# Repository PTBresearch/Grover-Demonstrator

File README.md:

# Grover-Demonstrator
A simple hardware demonstrator to let the user experience classical search in unstructured data, vs the Grover quantum computer algorithm.

## What can it be used for?

- [Showing how (computationally) hard it is to find something in unstructured data](#showing-how-computationally-hard-it-is-to-find-something-in-unstructured-data)
- [Showing the "quantum advantage" that the Grover algorithm can provide](#showing-the-quantum-advantage-that-the-grover-algorithm-can-provide)
- [Showing the relationship between shots and the probability distribution](#showing-the-relationship-between-shots-and-the-probability-distribution)
- [Showing the impact of noise on the results of quantum computers / the Grover algorithm](#showing-the-impact-of-noise-on-the-results-of-quantum-computers--the-grover-algorithm)
- [Attracting people to a booth by having it blink](#attracting-people-to-a-booth-by-having-it-blink)

## Device overview

| Control | Description |
|---|---|
| On/off switch (top) | Turns the demonstrator on/off. |
| Charging port (top) | Use a USB-A to USB-C cable. When fully charged, the device can run for ~15 h. |
| Model slider (top) | Selects one of the 3 models for "Quantum Computer" mode. |
| Round button (top right) | Switches between "Probability View" and "Shot View". Only in "Quantum Computer" mode. |
| "Classical Computer" button | Starts in "Classical Computer" mode. |
| "Quantum Computer" button | Starts in "Quantum Computer" mode. |
| Left display | Number of button presses needed the last time "Classical Computer" mode was used. |
| Right display | Number of button presses needed the last time "Quantum Computer" mode was used. |
| Blue button | Runs 1 iteration of the Grover algorithm. |
| 8 × 8 button grid | 64 buttons, one of which is searched. Non-pressed buttons light up based on the current view. |

## Showing how (computationally) hard it is to find something in unstructured data

1. Start the demonstrator in "Classical Computer" mode and give it to a user.
2. Their task is to find the one button (of the 64 square ones) that blinks green when pushed.
3. This is an example of search in unstructured data: the user has no idea which button will light green.
4. You can discuss with them that with 64 buttons, they will need 32 tries on average.

A good example of search in unstructured data is guessing a password or decrypting data with no information about the key. You can verify that a solution is correct (you can try to decrypt the data), but there are no strategies to speed up the search. This is different from search problems with structured data, where you can, for example, sort the data to make it easier to search through.

Buttons that have not been pressed glow in a blue hue. The brighter they are, the more likely they are the correct button. As the data are unstructured, all buttons glow equally bright, but they become brighter as fewer buttons are left to be pressed.

> [!TIP]
> If the user found the green button in just a few steps, you can ask them or someone else to try again.

## Showing the "quantum advantage" that the Grover algorithm can provide

1. The user should have used/seen the "Classical Computer" mode already.
2. Make sure the demonstrator uses the **"Ideal"** model.
3. Start "Quantum Computer" mode. The user must again find the green button, ideally with fewer button presses. You can either let them search or do it yourself.

Again, buttons that have not been pressed glow in a blue hue. The brighter they are, the more likely they are the correct button. Initially, all buttons are equally bright, as there is no information about the correct result.

The user can "spend" a button press by pressing the blue button, which causes the Grover search algorithm to improve the prediction of the button that is searched.

When the blue button has been pressed 6 times, the prediction will be best. You can "undo" blue button presses by pressing the "Classical Computer" button. This is sometimes helpful when explaining the algorithm.

Thus, the optimal strategy seems to be to press the blue button once, then the brightest button. This strategy is less ideal with noise and high shot costs.

## Showing the relationship between shots and the probability distribution

1. The user should have used/seen the "Classical Computer" mode already.
2. Start "Quantum Computer" mode. The user must again find the green button, ideally with fewer button presses. You can either let them search or do it yourself.
3. Press the round button at the top of the device to switch to "Shot" mode.

In Shot mode, the buttons do not glow based on their likelihood. Instead, individual shots of the quantum computer are simulated. After the Grover algorithm is computed, the quantum state is read out, resulting in one random result based on the probabilities given by the quantum state of the qubits.

This mode makes it much more difficult to find the correct result without the ideal number of Grover algorithm iterations (blue button presses), especially when the "Real" model is used.

## Showing the impact of noise on the results of quantum computers / the Grover algorithm

1. The user should have used/seen the "Classical Computer" mode already.
2. Start "Quantum Computer" mode. The user must again find the green button, ideally with fewer button presses. You can either let them search or do it yourself.
3. When the blue Grover button has been pressed a few times, use the slider at the top to change between models:
   - **Ideal**: Simulation of a quantum computer without any noise/errors.
   - **Model**: Simple error model that introduces some gate errors.
   - **Real**: Results from a real IBM quantum computer.

The difference between the models is most easily visible when the buttons show probabilities, but Shot mode can also be used.

## Attracting people to a booth by having it blink

1. Start the device in "Quantum Computer" mode and press the round button on the top to switch to "Shot" mode.
2. Place the demonstrator so people can see the buttons blinking.

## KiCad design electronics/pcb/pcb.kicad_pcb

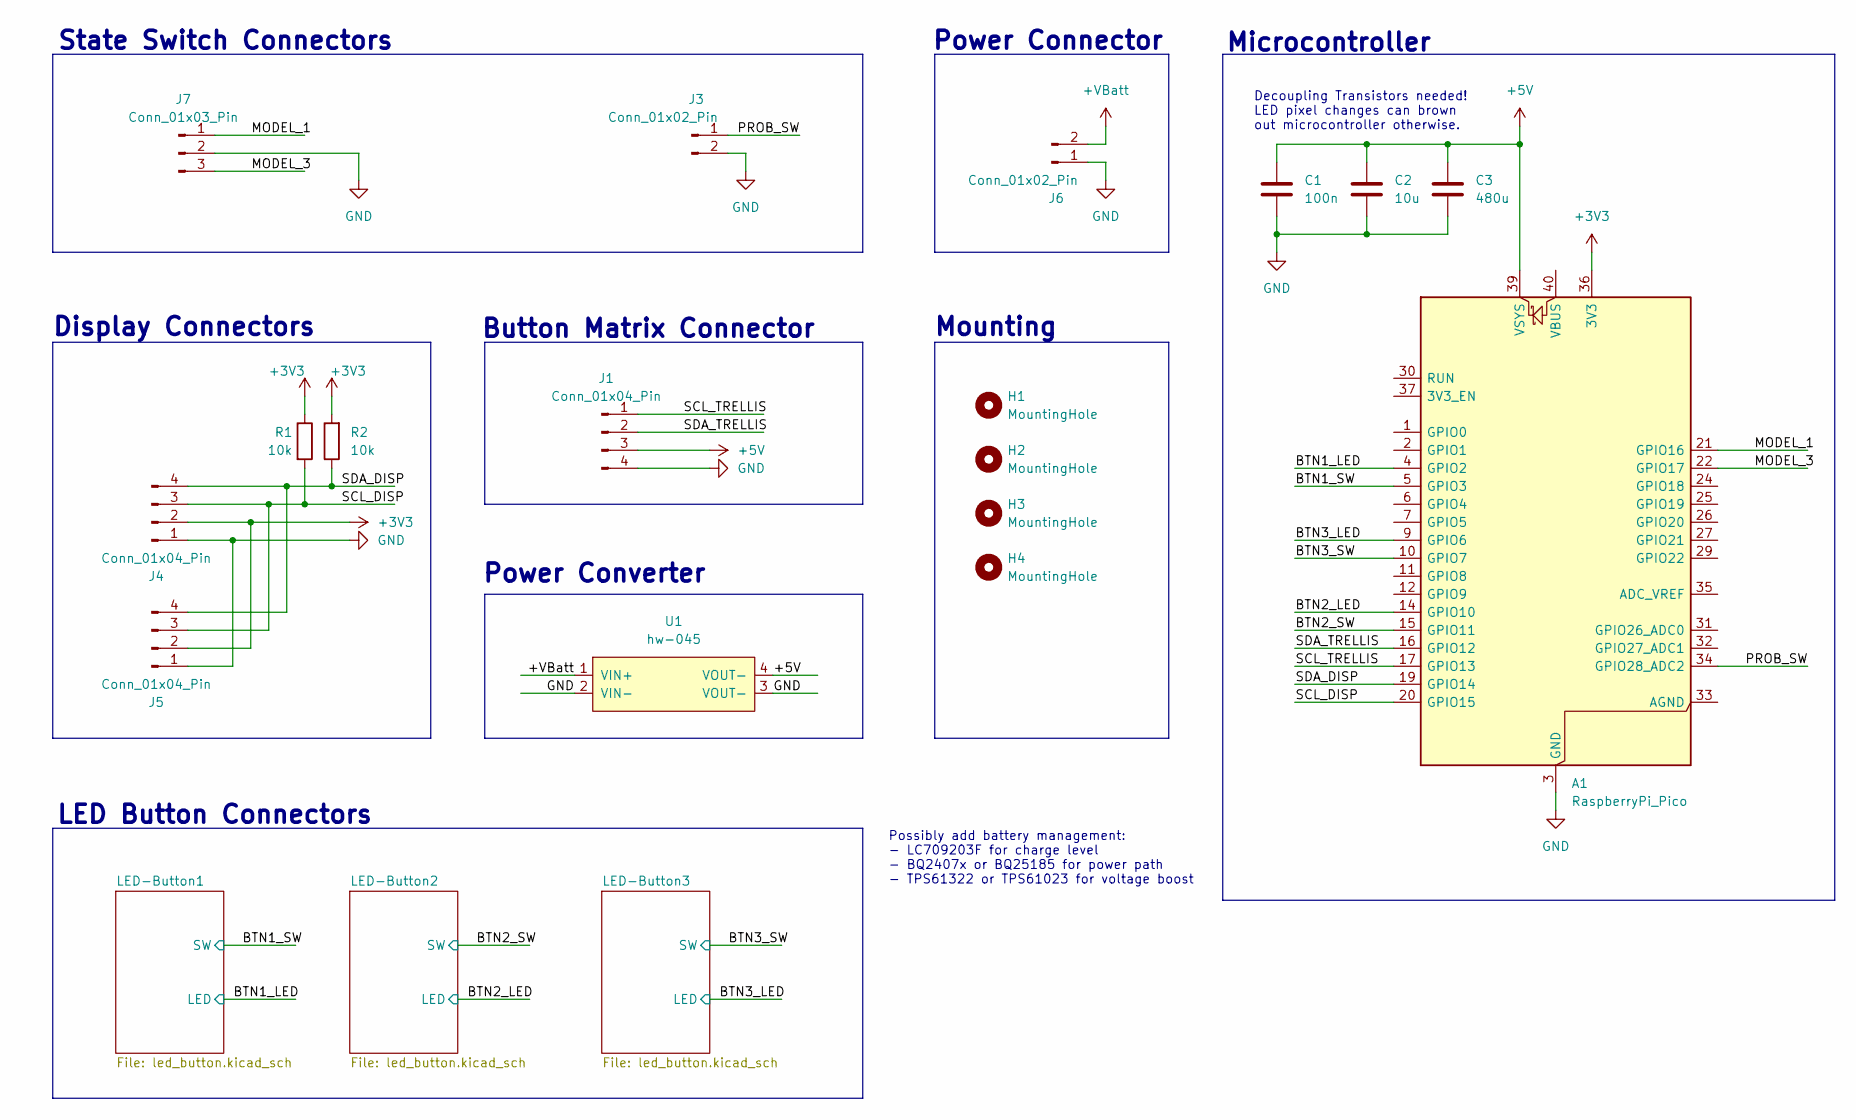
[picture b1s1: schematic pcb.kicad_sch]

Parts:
A1: RaspberryPi_Pico; RaspberryPi_Pico_Common_Unspecified
C1: 100n; C_Disc_D7.5mm_W5.0mm_P5.00mm
C2: 10u; CP_Radial_D5.0mm_P2.00mm
C3: 480u; CP_Radial_D12.5mm_P5.00mm
H1, H2, H3, H4: MountingHole; MountingHole_2.2mm_M2
J1, J4, J5: Conn_01x04_Pin; JST_PH_S4B-PH-K_1x04_P2.00mm_Horizontal
J3, J6: Conn_01x02_Pin; JST_PH_S2B-PH-K_1x02_P2.00mm_Horizontal
J7: Conn_01x03_Pin; JST_PH_S3B-PH-K_1x03_P2.00mm_Horizontal
R1, R2: 10k; R_Axial_DIN0309_L9.0mm_D3.2mm_P12.70mm_Horizontal
U1: hw-045

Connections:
+3V3: A1.36 (3V3), J4.2, J5.2, R1.1, R2.2
+5V: A1.39 (VSYS), C1.1, C2.1, C3.1, J1.3, U1.4 (VOUT-); also elsewhere on the board
+VBatt: J6.2, U1.1 (VIN+)
/BTN1_LED: A1.4 (GPIO2); also elsewhere on the board
/BTN1_SW: A1.5 (GPIO3); also elsewhere on the board
/BTN2_LED: A1.14 (GPIO10); also elsewhere on the board
/BTN2_SW: A1.15 (GPIO11); also elsewhere on the board
/BTN3_LED: A1.9 (GPIO6); also elsewhere on the board
/BTN3_SW: A1.10 (GPIO7); also elsewhere on the board
/MODEL_1: A1.21 (GPIO16), J7.1
/MODEL_3: A1.22 (GPIO17), J7.3
/PROB_SW: A1.34 (GPIO28_ADC2), J3.1
/SCL_DISP: A1.20 (GPIO15), J4.3, J5.3, R1.2
/SCL_TRELLIS: A1.17 (GPIO13), J1.1
/SDA_DISP: A1.19 (GPIO14), J4.4, J5.4, R2.1
/SDA_TRELLIS: A1.16 (GPIO12), J1.2
GND: A1.3 (GND), A1.8 (GND), A1.13 (GND), A1.18 (GND), A1.23 (GND), A1.28 (GND), A1.38 (GND), C1.2, C2.2, C3.2, J1.4, J3.2, J4.1, J5.1, J6.1, J7.2, U1.2 (VIN-), U1.3 (VOUT-); also elsewhere on the board

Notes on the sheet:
Display Connectors
State Switch Connectors
Possibly add battery management: - LC709203F for charge level - BQ2407x or BQ25185 for power path - TPS61322 or TPS61023 for voltage boost
Mounting
Power Converter
Power Connector
LED Button Connectors
Button Matrix Connector
Microcontroller
Decoupling Transistors needed! LED pixel changes can brown out microcontroller otherwise.

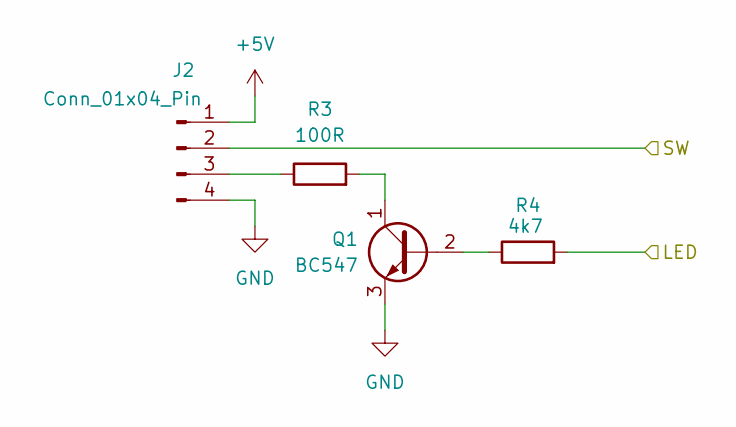
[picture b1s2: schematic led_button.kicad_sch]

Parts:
J2: Conn_01x04_Pin; JST_PH_S4B-PH-K_1x04_P2.00mm_Horizontal
Q1: BC547; TO-92_Inline_Wide
R3: 100R; R_Axial_DIN0309_L9.0mm_D3.2mm_P12.70mm_Horizontal
R4: 4k7; R_Axial_DIN0309_L9.0mm_D3.2mm_P12.70mm_Horizontal

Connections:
+5V: J2.1; also elsewhere on the board
/BTN3_LED: R4.2; also elsewhere on the board
/BTN3_SW: J2.2; also elsewhere on the board
GND: J2.4, Q1.3 (E); also elsewhere on the board
unnamed: J2.3, R3.1
unnamed: Q1.2 (B), R4.1
unnamed: Q1.1 (C), R3.2

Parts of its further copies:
J9, J10: Conn_01x04_Pin; JST_PH_S4B-PH-K_1x04_P2.00mm_Horizontal
Q2, Q3: BC547; TO-92_Inline_Wide
R5, R7: 100R; R_Axial_DIN0309_L9.0mm_D3.2mm_P12.70mm_Horizontal
R6, R8: 4k7; R_Axial_DIN0309_L9.0mm_D3.2mm_P12.70mm_Horizontal

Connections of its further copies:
+5V: J9.1, J10.1; also elsewhere on the board
/BTN1_LED: R6.2; also elsewhere on the board
/BTN1_SW: J9.2; also elsewhere on the board
/BTN2_LED: R8.2; also elsewhere on the board
/BTN2_SW: J10.2; also elsewhere on the board
GND: J9.4, J10.4, Q2.3 (E), Q3.3 (E); also elsewhere on the board
unnamed: J9.3, R5.1
unnamed: J10.3, R7.1
unnamed: Q2.2 (B), R6.1
unnamed: Q2.1 (C), R5.2
unnamed: Q3.2 (B), R8.1
unnamed: Q3.1 (C), R7.2

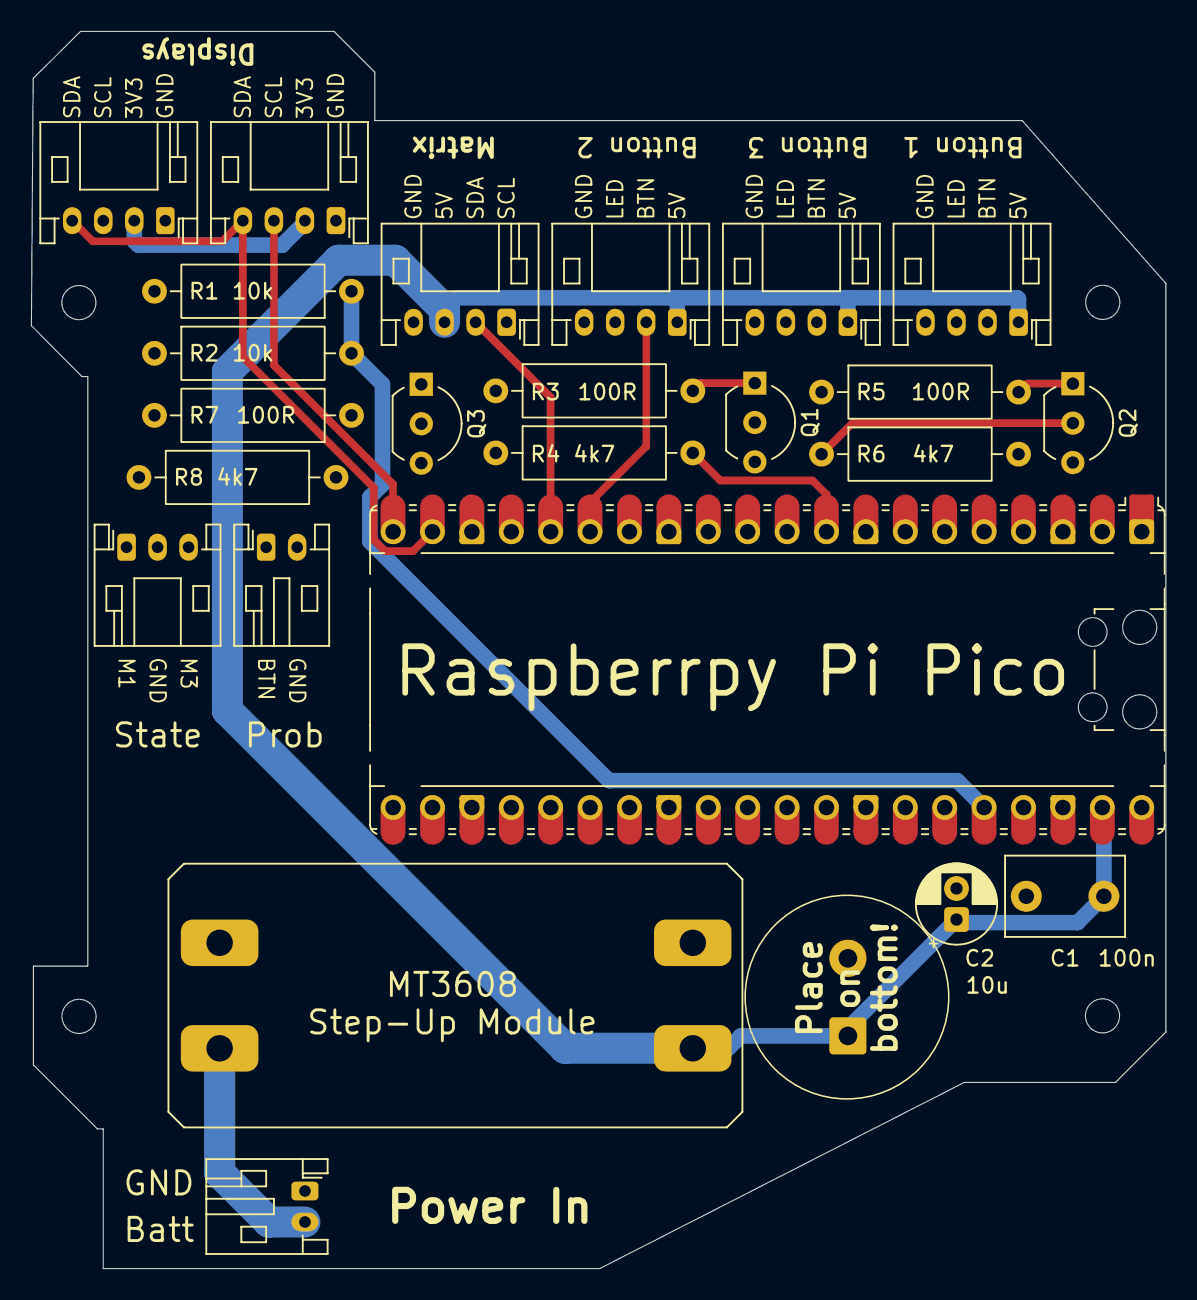
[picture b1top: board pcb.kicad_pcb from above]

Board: 4 copper layers, 73.1 x 79.8 mm, 29 parts (1 on the bottom side), 26 nets.
